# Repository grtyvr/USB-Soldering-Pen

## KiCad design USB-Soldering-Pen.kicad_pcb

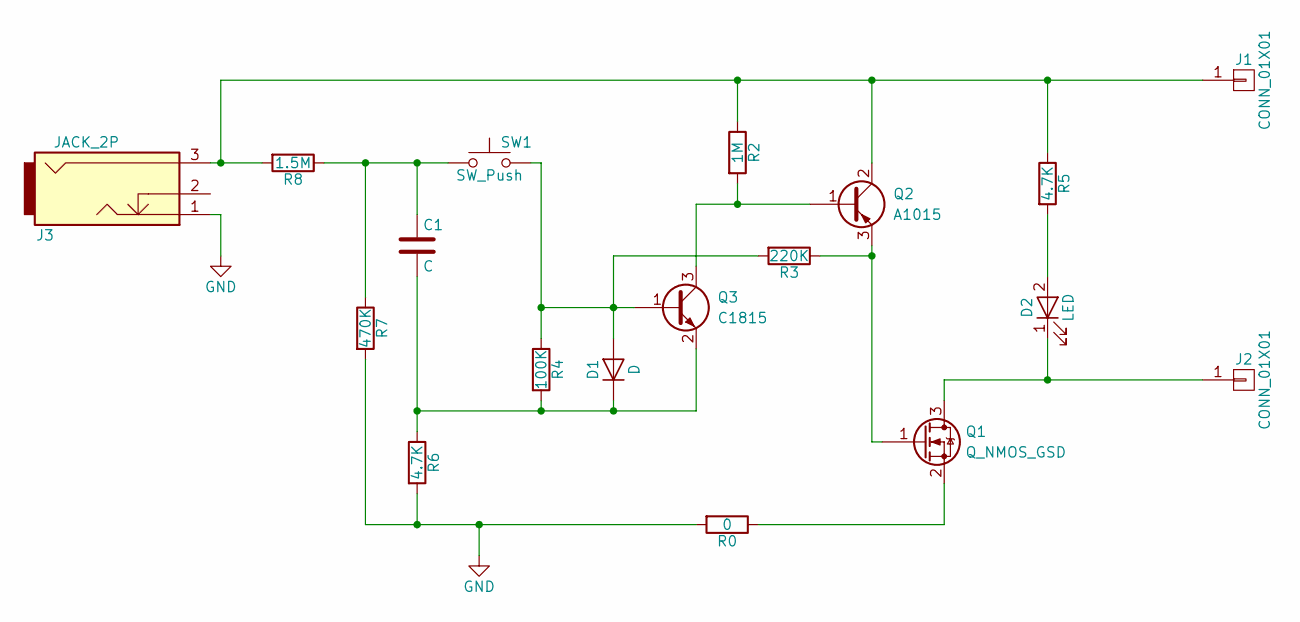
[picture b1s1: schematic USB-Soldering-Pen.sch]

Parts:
C1: C; C_0805_HandSoldering
D1: D; D_0603
D2: LED; LED_D3.0mm
J1, J2: CONN_01X01; SolderWirePad_single_1-5mmDrill
J3: JACK_2P; BARREL_JACK
Q1: Q_NMOS_GSD; SOT-23
Q2: A1015; SOT-23
Q3: C1815; SOT-23
R0: 0; R_0805_HandSoldering
R2: 1M; R_0603_HandSoldering
R3: 220K; R_0603_HandSoldering
R4: 100K; R_0603_HandSoldering
R5, R6: 4.7K; R_0603_HandSoldering
R7: 470K; R_0603_HandSoldering
R8: 1.5M; R_0603_HandSoldering
SW1: SW_Push; SW_PUSH_6mm_h4.3mm

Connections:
+5V: J1.1, J3.3, Q2.2 (C), R2.1, R5.1, R8.2
GND: J3.1, R0.2, R6.2, R7.2
unnamed: C1.1, R7.1, R8.1, SW1.1
unnamed: C1.2, D1.1 (K), Q3.2 (E), R4.2, R6.1
unnamed: D1.2 (A), Q3.1 (B), R3.2, R4.1, SW1.2
unnamed: D2.1 (K), J2.1, Q1.3 (D)
unnamed: D2.2 (A), R5.2
unnamed: Q1.1 (G), Q2.3 (E), R3.1
unnamed: Q1.2 (S), R0.1
unnamed: Q2.1 (B), Q3.3 (C), R2.2

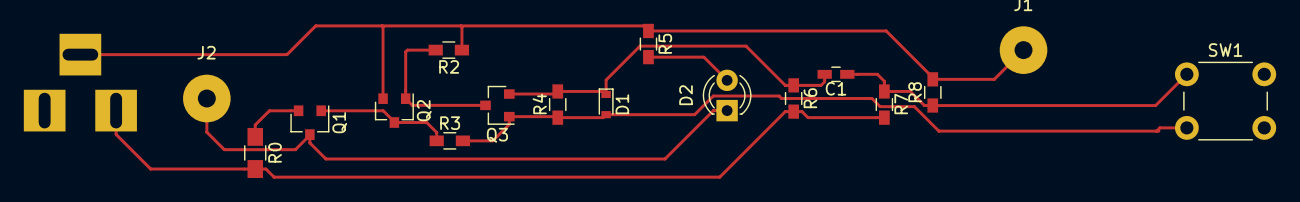
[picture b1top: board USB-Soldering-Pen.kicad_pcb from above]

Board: 2 copper layers, 18 parts (1 on the bottom side), 10 nets.

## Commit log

2018-04-10 added gitignore
